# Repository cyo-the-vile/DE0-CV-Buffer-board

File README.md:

# DE0-CV-Buffer-board
A buffer board to safely use a DE0-CV with 5V systems
This was meant to be a private project but I think it's appropriate to publicly share.

I made a quick voltage buffer board for my DE0-CV evaluation board.  The intent is to safely use the Signaltap software with 5V systems for reverse engineering.  

-You will need an IDC40 cable to connect to this board as it is intended to use a 2x20 2.54mm pin header for the FPGA connector that's labeled

-74HC541 in SOIC package is the voltage buffer being used.  OE1 and OE2 are grounded enabling bidirectional communication just in case you decide to use your FPGA to communicate to the target platform.  So this can be used not just for reverse engineering but for general communication to 5V platforms.

-I also provided 3 pins for ground, 5V and 3v3 just in case they need to be reached for peripherals.

-Silkscreen near the 8 pin clusters are the pins that it connects to on the GPIO port.  Notice some are skipped.  This is due to the GND, 3v3 and 5V lines from the GPIO port.  Please see the DE0-CV schematic if you're confused.

-Kicad files are provided; gerber files for fabrication are labeled.  I recommend JLCPCB :)

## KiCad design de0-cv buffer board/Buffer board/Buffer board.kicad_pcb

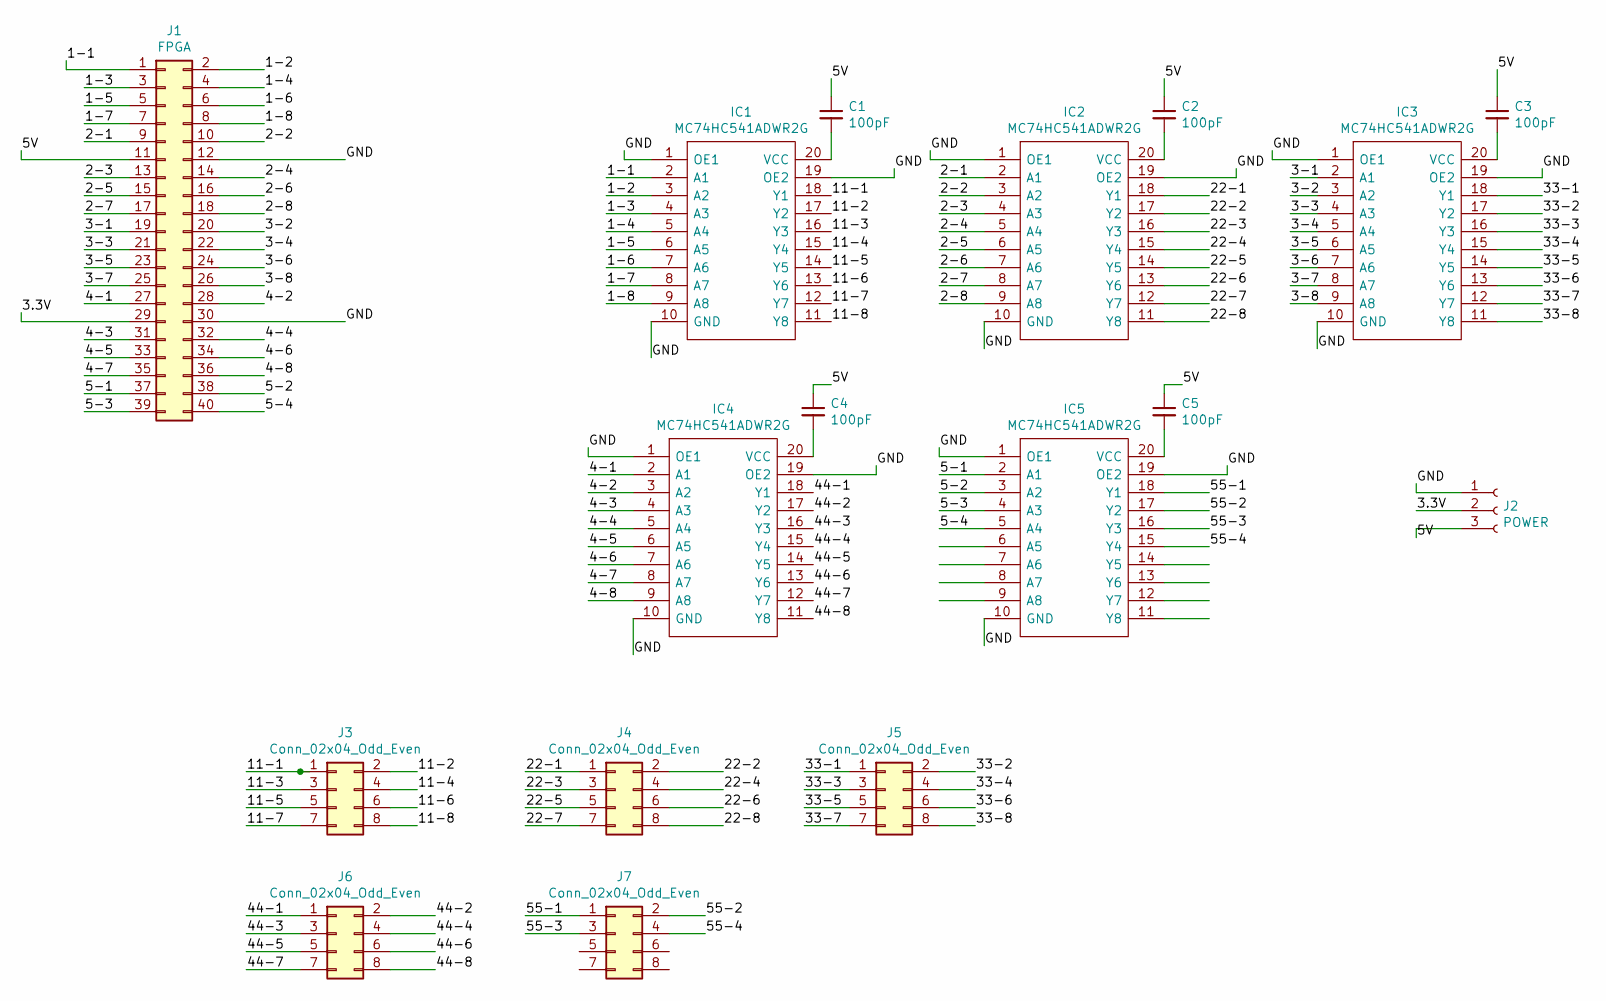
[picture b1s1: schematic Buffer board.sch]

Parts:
C1, C2, C3, C4, C5: 100pF; C_0805_2012Metric
IC1, IC2, IC3, IC4, IC5: MC74HC541ADWR2G; SOIC-20W_7.5x12.8mm_P1.27mm; Manufacturer_Part_Number MC74HC541ADWR2G; Mouser Part Number 863-MC74HC541ADWR2G
J1: FPGA; PinHeader_2x20_P2.54mm_Vertical
J2: POWER; PinHeader_1x03_P2.54mm_Vertical
J3, J4, J5, J6, J7: Conn_02x04_Odd_Even; PinSocket_2x04_P2.54mm_Vertical

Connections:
/1-1: IC1.2 (A1), J1.1
/1-2: IC1.3 (A2), J1.2
/1-3: IC1.4 (A3), J1.3
/1-4: IC1.5 (A4), J1.4
/1-5: IC1.6 (A5), J1.5
/1-6: IC1.7 (A6), J1.6
/1-7: IC1.8 (A7), J1.7
/1-8: IC1.9 (A8), J1.8
/2-1: IC2.2 (A1), J1.9
/2-2: IC2.3 (A2), J1.10
/2-3: IC2.4 (A3), J1.13
/2-4: IC2.5 (A4), J1.14
/2-5: IC2.6 (A5), J1.15
/2-6: IC2.7 (A6), J1.16
/2-7: IC2.8 (A7), J1.17
/2-8: IC2.9 (A8), J1.18
/3-1: IC3.2 (A1), J1.19
/3-2: IC3.3 (A2), J1.20
/3-3: IC3.4 (A3), J1.21
/3-4: IC3.5 (A4), J1.22
/3-5: IC3.6 (A5), J1.23
/3-6: IC3.7 (A6), J1.24
/3-7: IC3.8 (A7), J1.25
/3-8: IC3.9 (A8), J1.26
/3.3V: J1.29, J2.2
/4-1: IC4.2 (A1), J1.27
/4-2: IC4.3 (A2), J1.28
/4-3: IC4.4 (A3), J1.31
/4-4: IC4.5 (A4), J1.32
/4-5: IC4.6 (A5), J1.33
/4-6: IC4.7 (A6), J1.34
/4-7: IC4.8 (A7), J1.35
/4-8: IC4.9 (A8), J1.36
/5-1: IC5.2 (A1), J1.37
/5-2: IC5.3 (A2), J1.38
/5-3: IC5.4 (A3), J1.39
/5-4: IC5.5 (A4), J1.40
/5V: C1.1, C2.1, C3.1, C4.1, C5.1, J1.11, J2.3
/11-1: IC1.18 (Y1), J3.1
/11-2: IC1.17 (Y2), J3.2
/11-3: IC1.16 (Y3), J3.3
/11-4: IC1.15 (Y4), J3.4
/11-5: IC1.14 (Y5), J3.5
/11-6: IC1.13 (Y6), J3.6
/11-7: IC1.12 (Y7), J3.7
/11-8: IC1.11 (Y8), J3.8
/22-1: IC2.18 (Y1), J4.1
/22-2: IC2.17 (Y2), J4.2
/22-3: IC2.16 (Y3), J4.3
/22-4: IC2.15 (Y4), J4.4
/22-5: IC2.14 (Y5), J4.5
/22-6: IC2.13 (Y6), J4.6
/22-7: IC2.12 (Y7), J4.7
/22-8: IC2.11 (Y8), J4.8
/33-1: IC3.18 (Y1), J5.1
/33-2: IC3.17 (Y2), J5.2
/33-3: IC3.16 (Y3), J5.3
/33-4: IC3.15 (Y4), J5.4
/33-5: IC3.14 (Y5), J5.5
/33-6: IC3.13 (Y6), J5.6
/33-7: IC3.12 (Y7), J5.7
/33-8: IC3.11 (Y8), J5.8
/44-1: IC4.18 (Y1), J6.1
/44-2: IC4.17 (Y2), J6.2
/44-3: IC4.16 (Y3), J6.3
/44-4: IC4.15 (Y4), J6.4
/44-5: IC4.14 (Y5), J6.5
/44-6: IC4.13 (Y6), J6.6
/44-7: IC4.12 (Y7), J6.7
/44-8: IC4.11 (Y8), J6.8
/55-1: IC5.18 (Y1), J7.1
/55-2: IC5.17 (Y2), J7.2
/55-3: IC5.16 (Y3), J7.3
/55-4: IC5.15 (Y4), J7.4
/GND: IC1.1 (OE1), IC1.10 (GND), IC1.19 (OE2), IC2.1 (OE1), IC2.10 (GND), IC2.19 (OE2), IC3.1 (OE1), IC3.10 (GND), IC3.19 (OE2), IC4.1 (OE1), IC4.10 (GND), IC4.19 (OE2), IC5.1 (OE1), IC5.10 (GND), IC5.19 (OE2), J1.12, J1.30, J2.1
unnamed: C1.2, IC1.20 (VCC)
unnamed: C2.2, IC2.20 (VCC)
unnamed: C3.2, IC3.20 (VCC)
unnamed: C4.2, IC4.20 (VCC)
unnamed: C5.2, IC5.20 (VCC)

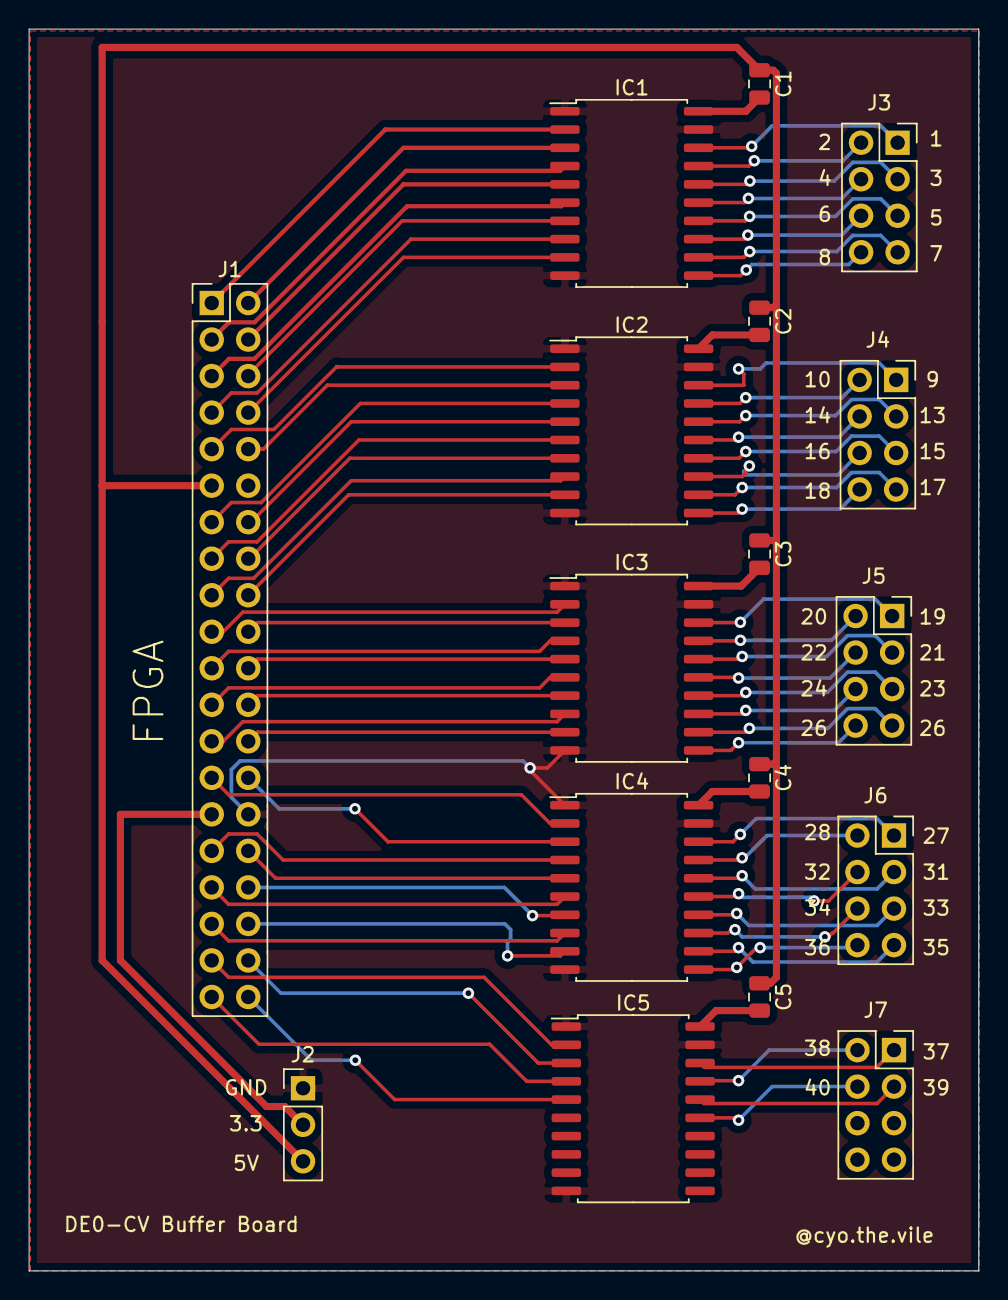
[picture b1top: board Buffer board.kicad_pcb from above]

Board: 2 copper layers, 66.0 x 86.4 mm, 17 parts (0 on the bottom side), 80 nets.
